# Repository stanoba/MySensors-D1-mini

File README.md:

# MySensors-D1-mini
MySensors D1 mini is derivative of <a href="https://www.openhardware.io/view/1/Sensebender-Micro" target="_blank">Sensebender Micro</a> designed by Thomas Mørch (thomas@mysensors.org).
Main goal of this project is to use all <a href="https://www.wemos.cc/D1-mini-Shields" target="_blank">Wemos D1 mini (pro) shields</a> (not tested yet, draft) with MySensors node.

You can order PCB from following two sources:<ul>
<li><a href="https://pcbs.io/share/zdVkg" target="_blank">PCBs.io</a> 4 for $6, black 1.6mm PCB</li>
<li><a href="https://oshpark.com/projects/yifTZHL4" target="_blank">OSHPark.com</a> 3 for $7.60, purple 1.6mm PCB</li>
<ul/>

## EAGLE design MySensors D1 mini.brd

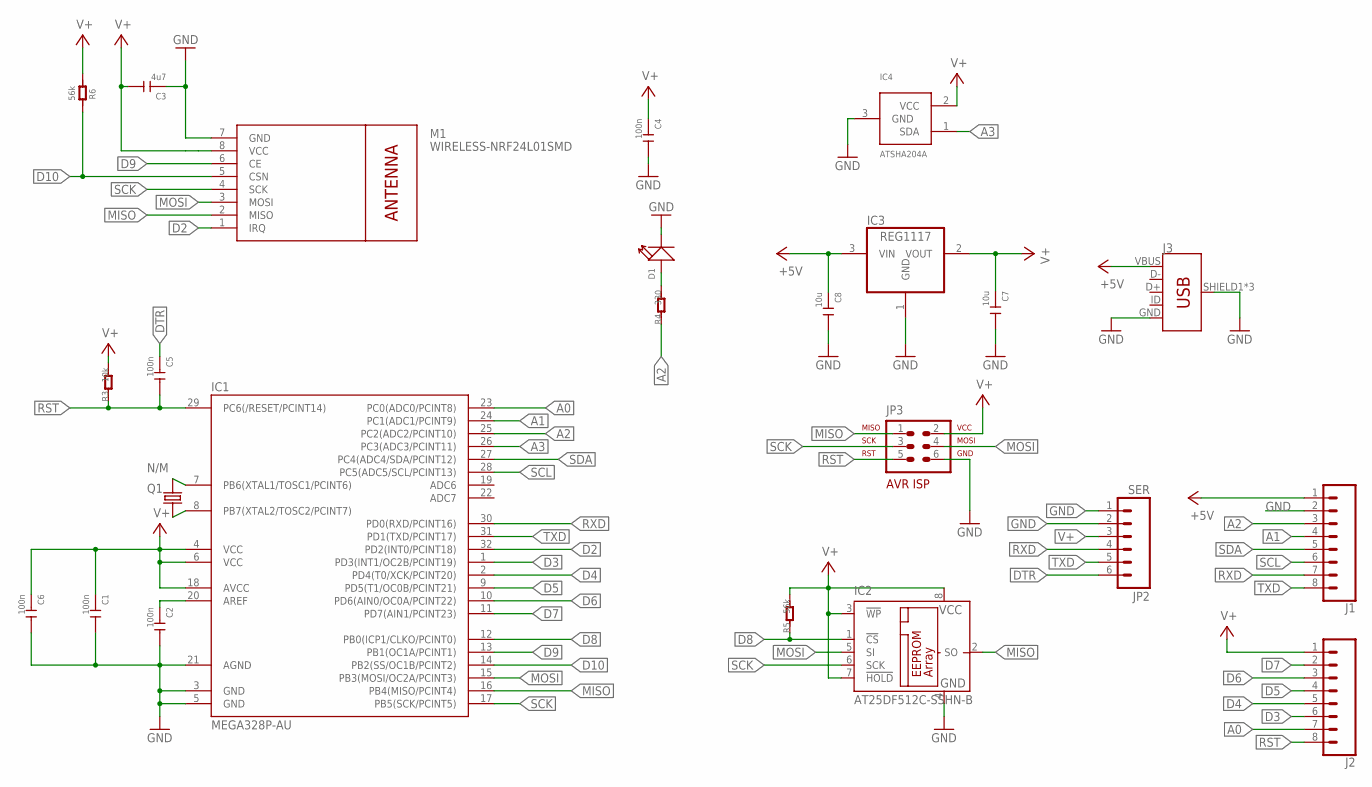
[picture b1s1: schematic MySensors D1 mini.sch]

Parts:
C1, C2, C4, C5, C6: 100n; C0402
C3: 4u7; C0603
C7, C8: 10u; C1206
D1: LED-0402
IC1: MEGA328P-AU; TQFP32-08
IC2: AT25DF512C-SSHN-B; SO-08
IC3: REG1117; SOT223
IC4: ATSHA204A; SOT23
J1, J2: CONN_08"; 1X08
J3: USB_MICRO-B_FEMALE-SMT; USB-B-MICRO-SMD
JP2: SER; 1X06_NO_SILK
JP3: N/M; AVR-ISP-6
M1: WIRELESS-NRF24L01SMD; WIRELESS-NRF24L01-SMD
Q1: N/M; 2P-L3.2XW1.5MM
R3: 10k; R0402
R4: 330; R0402
R5, R6: 56k; R0402

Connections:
+5V: C8.1, IC3.3 (VIN), J1.1, J3.VBUS
A0: IC1.23 (PC0(ADC0/PCINT8)), J2.7
A1: IC1.24 (PC1(ADC1/PCINT9)), J1.4
A2: IC1.25 (PC2(ADC2/PCINT10)), J1.3, R4.1
A3: IC1.26 (PC3(ADC3/PCINT11)), IC4.1 (SDA)
D2: IC1.32 (PD2(INT0/PCINT18)), M1.1 (IRQ)
D3: IC1.1 (PD3(INT1/OC2B/PCINT19)), J2.6
D4: IC1.2 (PD4(T0/XCK/PCINT20)), J2.5
D5: IC1.9 (PD5(T1/OC0B/PCINT21)), J2.4
D6: IC1.10 (PD6(AIN0/OC0A/PCINT22)), J2.3
D7: IC1.11 (PD7(AIN1/PCINT23)), J2.2
D8: IC1.12 (PB0(ICP1/CLKO/PCINT0)), IC2.1 (!CS), R5.1
D9: IC1.13 (PB1(OC1A/PCINT1)), M1.6 (CE)
D10: IC1.14 (PB2(SS/OC1B/PCINT2)), M1.5 (CSN), R6.1
DTR: C5.1, JP2.6
GND: C1.2, C2.2, C3.1, C4.2, C6.2, C7.2, C8.2, D1.-, IC1.3 (GND), IC1.5 (GND), IC1.21 (AGND), IC2.4 (GND), IC3.1 (GND), IC4.3 (GND), J1.2, J3.GND, J3.SHIELD1 (SHIELD), J3.SHIELD2 (SHIELD), J3.SHIELD3 (SHIELD), JP2.1, JP2.2, JP3.6, M1.7 (GND)
MISO: IC1.16 (PB4(MISO/PCINT4)), IC2.2 (SO), JP3.1, M1.2 (MISO)
MOSI: IC1.15 (PB3(MOSI/OC2A/PCINT3)), IC2.5 (SI), JP3.4, M1.3 (MOSI)
unnamed: IC1.7 (PB6(XTAL1/TOSC1/PCINT6)), Q1.1
unnamed: IC1.8 (PB7(XTAL2/TOSC2/PCINT7)), Q1.2
unnamed: D1.+, R4.2
unnamed: C2.1, IC1.20 (AREF)
RST: C5.2, IC1.29 (PC6(/RESET/PCINT14)), J2.8, JP3.5, R3.1
RXD: IC1.30 (PD0(RXD/PCINT16)), J1.7, JP2.4
SCK: IC1.17 (PB5(SCK/PCINT5)), IC2.6 (SCK), JP3.3, M1.4 (SCK)
SCL: IC1.28 (PC5(ADC5/SCL/PCINT13)), J1.6
SDA: IC1.27 (PC4(ADC4/SDA/PCINT12)), J1.5
TXD: IC1.31 (PD1(TXD/PCINT17)), J1.8, JP2.5
V+: C1.1, C3.2, C4.1, C6.1, C7.1, IC1.4 (VCC), IC1.6 (VCC), IC1.18 (AVCC), IC2.3 (!WP), IC2.7 (!HOLD), IC2.8 (VCC), IC3.2 (VOUT), IC4.2 (VCC), J2.1, JP2.3, JP3.2, M1.8 (VCC), R3.2, R5.2, R6.2

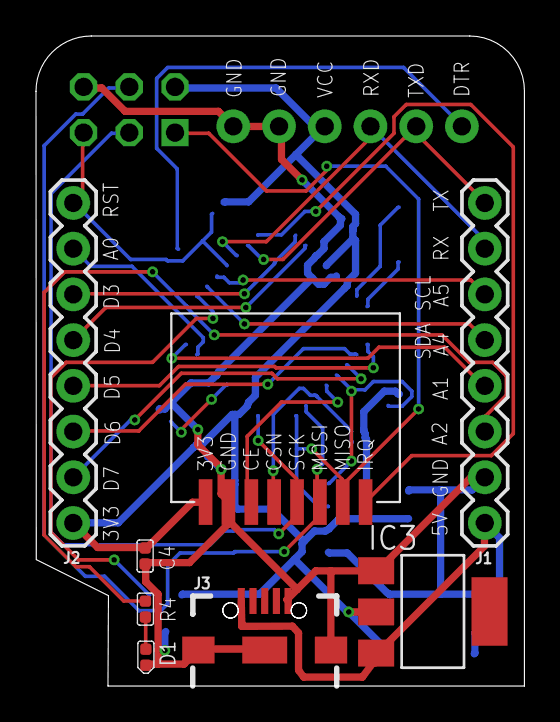
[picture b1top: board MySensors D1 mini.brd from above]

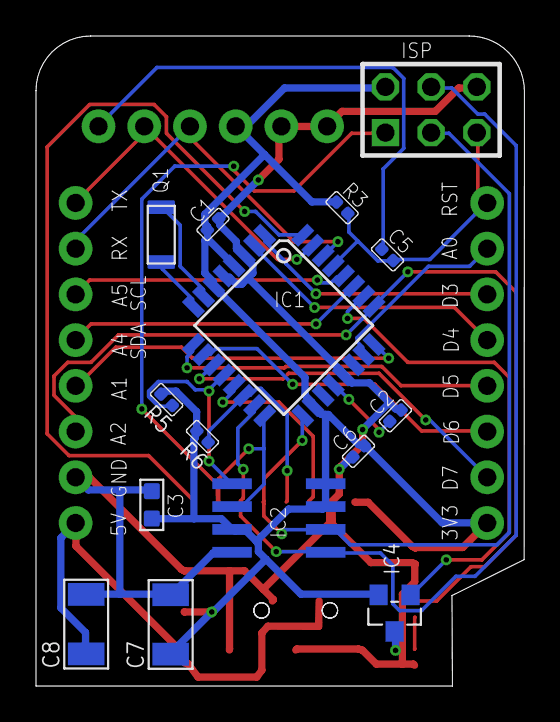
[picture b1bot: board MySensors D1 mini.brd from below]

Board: 2 copper layers, 27.1 x 36.1 mm, 24 parts (16 on the bottom side), 29 nets.

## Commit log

2017-03-20 initial release v0.1 (draft)
2017-03-21 License
2017-03-21 Updated labels, fixed issue with MicroUSB

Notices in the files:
parts and their libraries:
SparkFun-Connectors: Licensing: Creative Commons ShareAlike 4.0 International - https://creativecommons.org/licenses/by-sa/4.0
